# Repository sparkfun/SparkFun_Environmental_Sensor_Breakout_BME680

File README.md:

SparkFun Environmental Sensor - BME680 (Qwiic)
========================================

[*SparkFun Environmental Sensor - BME680 (Qwiic) (SEN-16466)*](https://www.sparkfun.com/products/16466)

The Environmental Sensor - BME680 (Qwiic) is a powerful 4-in-1 environmental sensor that communicates over I<sup>2</sup>C or SPI. The BME680 combines a gas sensor with temperature, humidity and barometric pressure sensors for a complete environmental sensor in a tiny package.

Repository Contents
-------------------
* **/Hardware** - Eagle design files (.brd, .sch)
* **/Production** - Production panel files (.brd)

Documentation
--------------
* **[Hookup Guide](https://learn.sparkfun.com/tutorials/environmental-sensor---bme680-qwiic-hookup-guide)** - Basic hookup guide for the SparkFun Environmental Sensor - BME680 (Qwiic).
* **[BME680 Arduino Library](https://github.com/SV-Zanshin/BME680)** - Arduino library created by SV-Zanshin for the BME680 Environmental Sensor.
* **[SparkFun Fritzing repo](https://github.com/sparkfun/Fritzing_Parts)** - Fritzing diagrams for SparkFun products.
* **[SparkFun 3D Model repo](https://github.com/sparkfun/3D_Models)** - 3D models of SparkFun products. 

Product Versions
----------------
* [SPX-14570](https://www.sparkfun.com/products/14570)- Original SparkX Release.
* [SEN-16466](https://www.sparkfun.com/products/16466)- SparkFun release.

License Information
-------------------

This product is _**open source**_! 

Please review the LICENSE.md file for license information. 

If you have any questions or concerns on licensing, please contact technical support on our [SparkFun forums](https://forum.sparkfun.com/viewforum.php?f=152).

Distributed as-is; no warranty is given.

- Your friends at SparkFun.

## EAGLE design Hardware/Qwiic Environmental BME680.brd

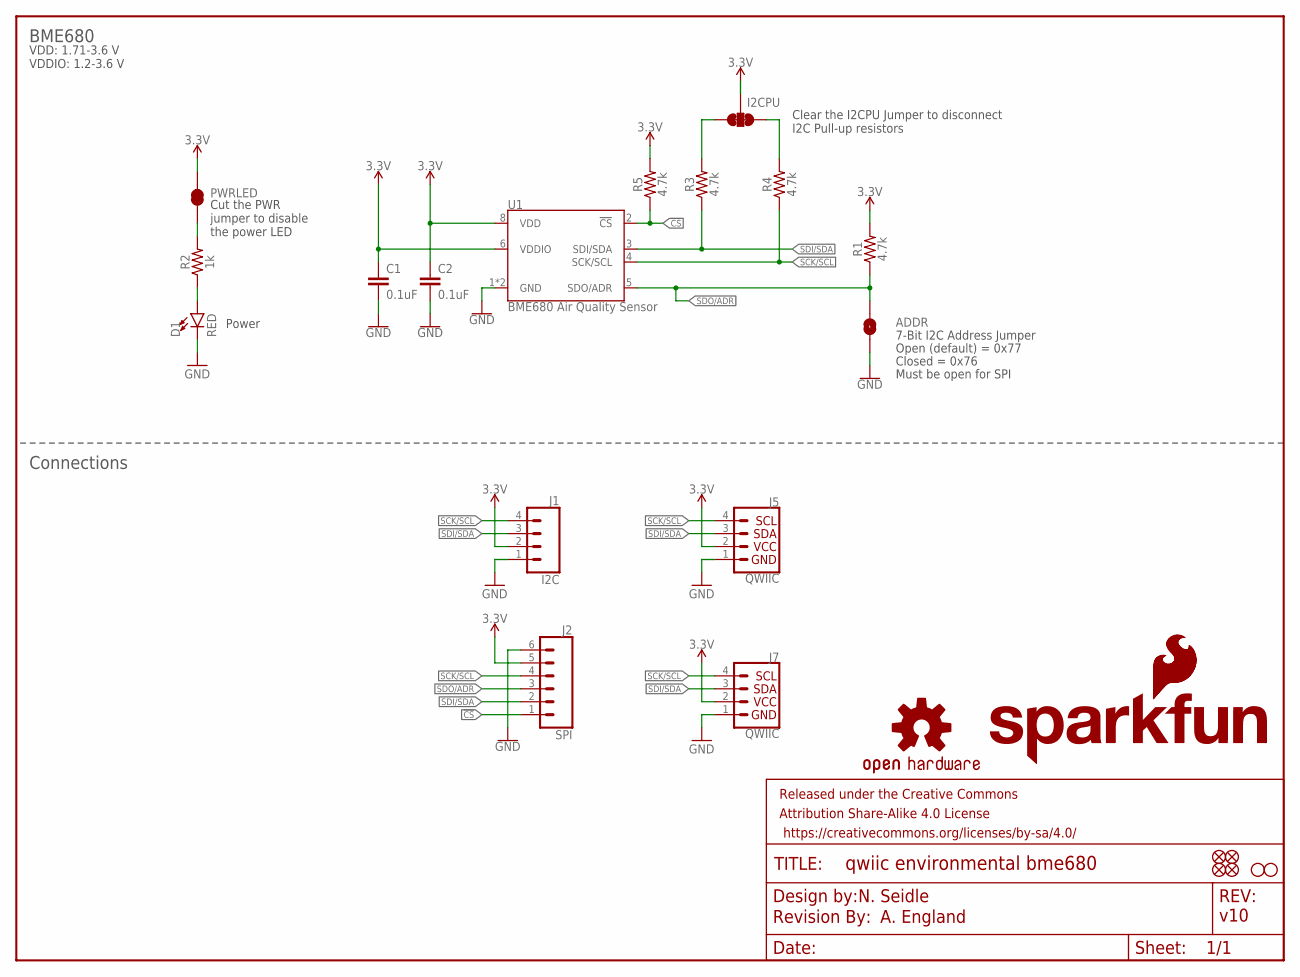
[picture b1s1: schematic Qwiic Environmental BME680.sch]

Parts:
ADDR: JUMPER-SMT_2_NO_SILK; SMT-JUMPER_2_NO_SILK
C1, C2: 0.1uF; 0603
D1: RED; LED-0603
FD1, FD2, FD3, FD4: FIDUCIALUFIDUCIAL; FIDUCIAL-MICRO
FRAME1: FRAME-LETTER; CREATIVE_COMMONS
H1, H2: STAND-OFFTIGHT; STAND-OFF-TIGHT
I2CPU: I2C PU; SMT-JUMPER_3_2-NC_TRACE_SILK
J1: I2C; 1X04_NO_SILK
J2: SPI; 1X06_NO_SILK
J5, J7: QWIIC; JST04_1MM_RA
LOGO1: OSHW-LOGOMINI; OSHW-LOGO-MINI
LOGO2: SFE_LOGO_NAME_FLAME.1_INCH; SFE_LOGO_NAME_FLAME_.1
LOGO3: REVISION
LOGO4: SFE_LOGO_FLAME.1_INCH; SFE_LOGO_FLAME_.1
PWRLED: JUMPER-SMT_2_NC_TRACE_SILK; SMT-JUMPER_2_NC_TRACE_SILK
R1, R3, R4, R5: 4.7k; 0603@1
R2: 1k; 0603
U1: BME680 Air Quality Sensor; LGA3.0X3.0

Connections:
3.3V: C1.1, C2.1, I2CPU.2, J1.2, J2.5, J5.2, J7.2, PWRLED.2, R1.2, R5.2, U1.6 (VDDIO), U1.8 (VDD)
!CS: J2.1, R5.1, U1.2 (!CS)
GND: ADDR.1, C1.2, C2.2, D1.C, J1.1, J2.6, J5.1, J7.1, U1.1 (GND), U1.7 (GND)
unnamed: PWRLED.1, R2.2
unnamed: D1.A, R2.1
unnamed: I2CPU.3, R3.2
unnamed: I2CPU.1, R4.2
SCK/SCL: J1.4, J2.4, J5.4, J7.4, R4.1, U1.4 (SCK/SCL)
SDI/SDA: J1.3, J2.2, J5.3, J7.3, R3.1, U1.3 (SDI/SDA)
SDO/ADR: ADDR.2, J2.3, R1.1, U1.5 (SDO/ADR)

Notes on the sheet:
v10
7-Bit I2C Address Jumper
Open (default) = 0x77
Closed = 0x76
N. Seidle
BME680
Connections
A. England
VDD: 1.71-3.6 V VDDIO: 1.2-3.6 V
Must be open for SPI
Clear the I2CPU Jumper to disconnect I2C Pull-up resistors
Power
Cut the PWR jumper to disable the power LED

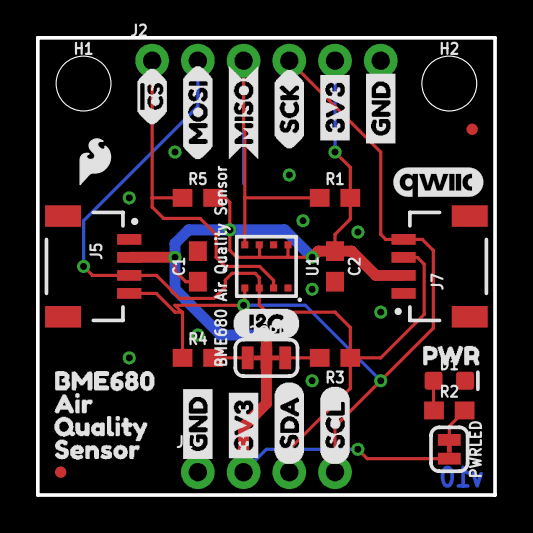
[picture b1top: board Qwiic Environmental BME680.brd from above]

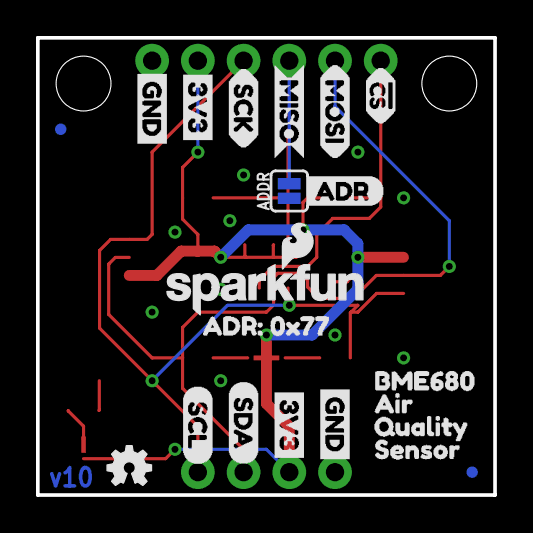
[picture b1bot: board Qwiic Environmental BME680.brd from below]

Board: 2 copper layers, 25.4 x 25.4 mm, 60 parts (21 on the bottom side), 10 nets.

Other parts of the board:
U$1, U$2: MISO_O
U$3, U$4: !CS_I
U$5, U$6: MOSI_I
U$7, U$8: SCK_I
U$9, U$10, U$16, U$17: 3V3_P
U$11, U$12, U$13, U$14: GND_P
U$15: I2C
U$18, U$19: SDA_IO
U$20, U$21: SCL_IO
U$22, U$26: BME6800
U$23, U$27: AIR1
U$24, U$28: QUALITY2
U$25, U$29: SENSOR3
U$30: ADR4
U$32: QWIIC_5MM
U$33: ADR#_0X770
U$34: PWR_TO

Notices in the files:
parts and their libraries:
SparkFun-Capacitors: Licensing: Creative Commons ShareAlike 4.0 International - https://creativecommons.org/licenses/by-sa/4.0
SparkFun-Aesthetics: Released under the Creative Commons Attribution Share-Alike 4.0 License
SparkFun-Aesthetics: https://creativecommons.org/licenses/by-sa/4.0
